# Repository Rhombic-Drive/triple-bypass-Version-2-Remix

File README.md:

# Triple Bypass Version 2
This is a redesign of the fantastic 3bp from dbElectronics.  The goal of this project was to take the initial design and accommodate all models on one pcb without the need to swap parts. It was a team effort between myself, Retrorgb, and Jose Cruz who did the majorty of the testing. Ace, FirebrandX and Mobiusstriptech all were part of the group that helped with the redesign and added various ideas and suggestions that lead to the final product.  The audio adjustment work was done with the help of the mdFourier tool by Artemio Urbina found here - 
https://github.com/ArtemioUrbina/MDFourier.  Artemio and Bfbii stayed up many late nights and helped me run mdFourier to get the levels to match as close as we could to a model 1 va3 genesis.

From zaxour:
Modified version of Tian Feng/dB_Electronics triple bypass v2 board

Incorporates 5.6k pull up resistors for the RGB lines, as Model 1 3BP installs lift the VDP pins to isolate them from the Genesis/MD PCB. Based on research by Tian Feng, and subsequently verified by myself by looking at all available schematics for the Model 1 Genesis/MD, this causes a loss of fidelity in color transitions.

# Installation Instructions

Currently I suggest using the Audio installation instructions from the mega amp 2.0
http://www.sega-16.com/forum/showthread.php?31989-Take-your-Genesis-audio-to-the-next-level-The-Mega-Amp-2-0-is-here!

For rgb bypass instructions, please see https://www.retrorgb.com/genesistriplebypass.html for now. I will continue working on getting more up-to-date instructions.

# Confirmed Working
The current version of this is working with no issues and has been tested and measured with mdFourier. There are still some systems where the pull down jumpers have not been confirmed.  If you notice any issues, please let me know.
# Design Files
I designed this using the online software tool Easyeda. While I have made the file open for people to edit, I have not yet been able to allow for the files to be truly open source.  This is a work in progress and if I have to remake everything from scratch in Kicad. The files here will always be the most up to date versions. 
# Change Log 17/03/2020
I have added a kicad file to the folder.  it looks ok but I still see some issues with ground layers.  I am new to kicad but this pretty damn close.  As it stands, I still recommend using the current gerber files to send to a pcd fab.  The design files are good to go if you want to to change or modify the design.  
# Change Log 06/03/2020
- Changed the jumper settings on the silk screen to match new info from Jose Cruz that the model 2 va4 has all of the 75 ohm pulldowns on the Genesis. Nothing needs to be changed on the previous versions.  Just take note when installing in a model 2 va4.
# Change Log from V1
 - Added jumpers so that all pulldowns could be enabled or disabled without switching parts.
 - Added AC coupling capacitors on the input of the ths7374 to accommodate for systems that we have not measured or installed in yet.
 - Changed the op amp to a soic8 footprint to accommodate a larger variety of possible op amps.
 - Changed the op amp to a tl972 low noise op amp.
 - Lowered the overall volume and increased resistance to try and alleviate some of the clipping in the louder games.
 - Changed the resistor values and numbering to try and fit on the smaller board.
 - Changed audio and video capacitors to tantalum to accommodate for a bottom mount. 
 - Adjusted and tested installation in a model 1 Genesis. 
 - Increased the audio output capacitors to 47uf.
 - Shrunk the overall size and move the din to the middle of the board to try to avoid the power jacks on a bottom install. 
 - Changed the Low pass filter to a solder jumper that will enable when it is jumped.

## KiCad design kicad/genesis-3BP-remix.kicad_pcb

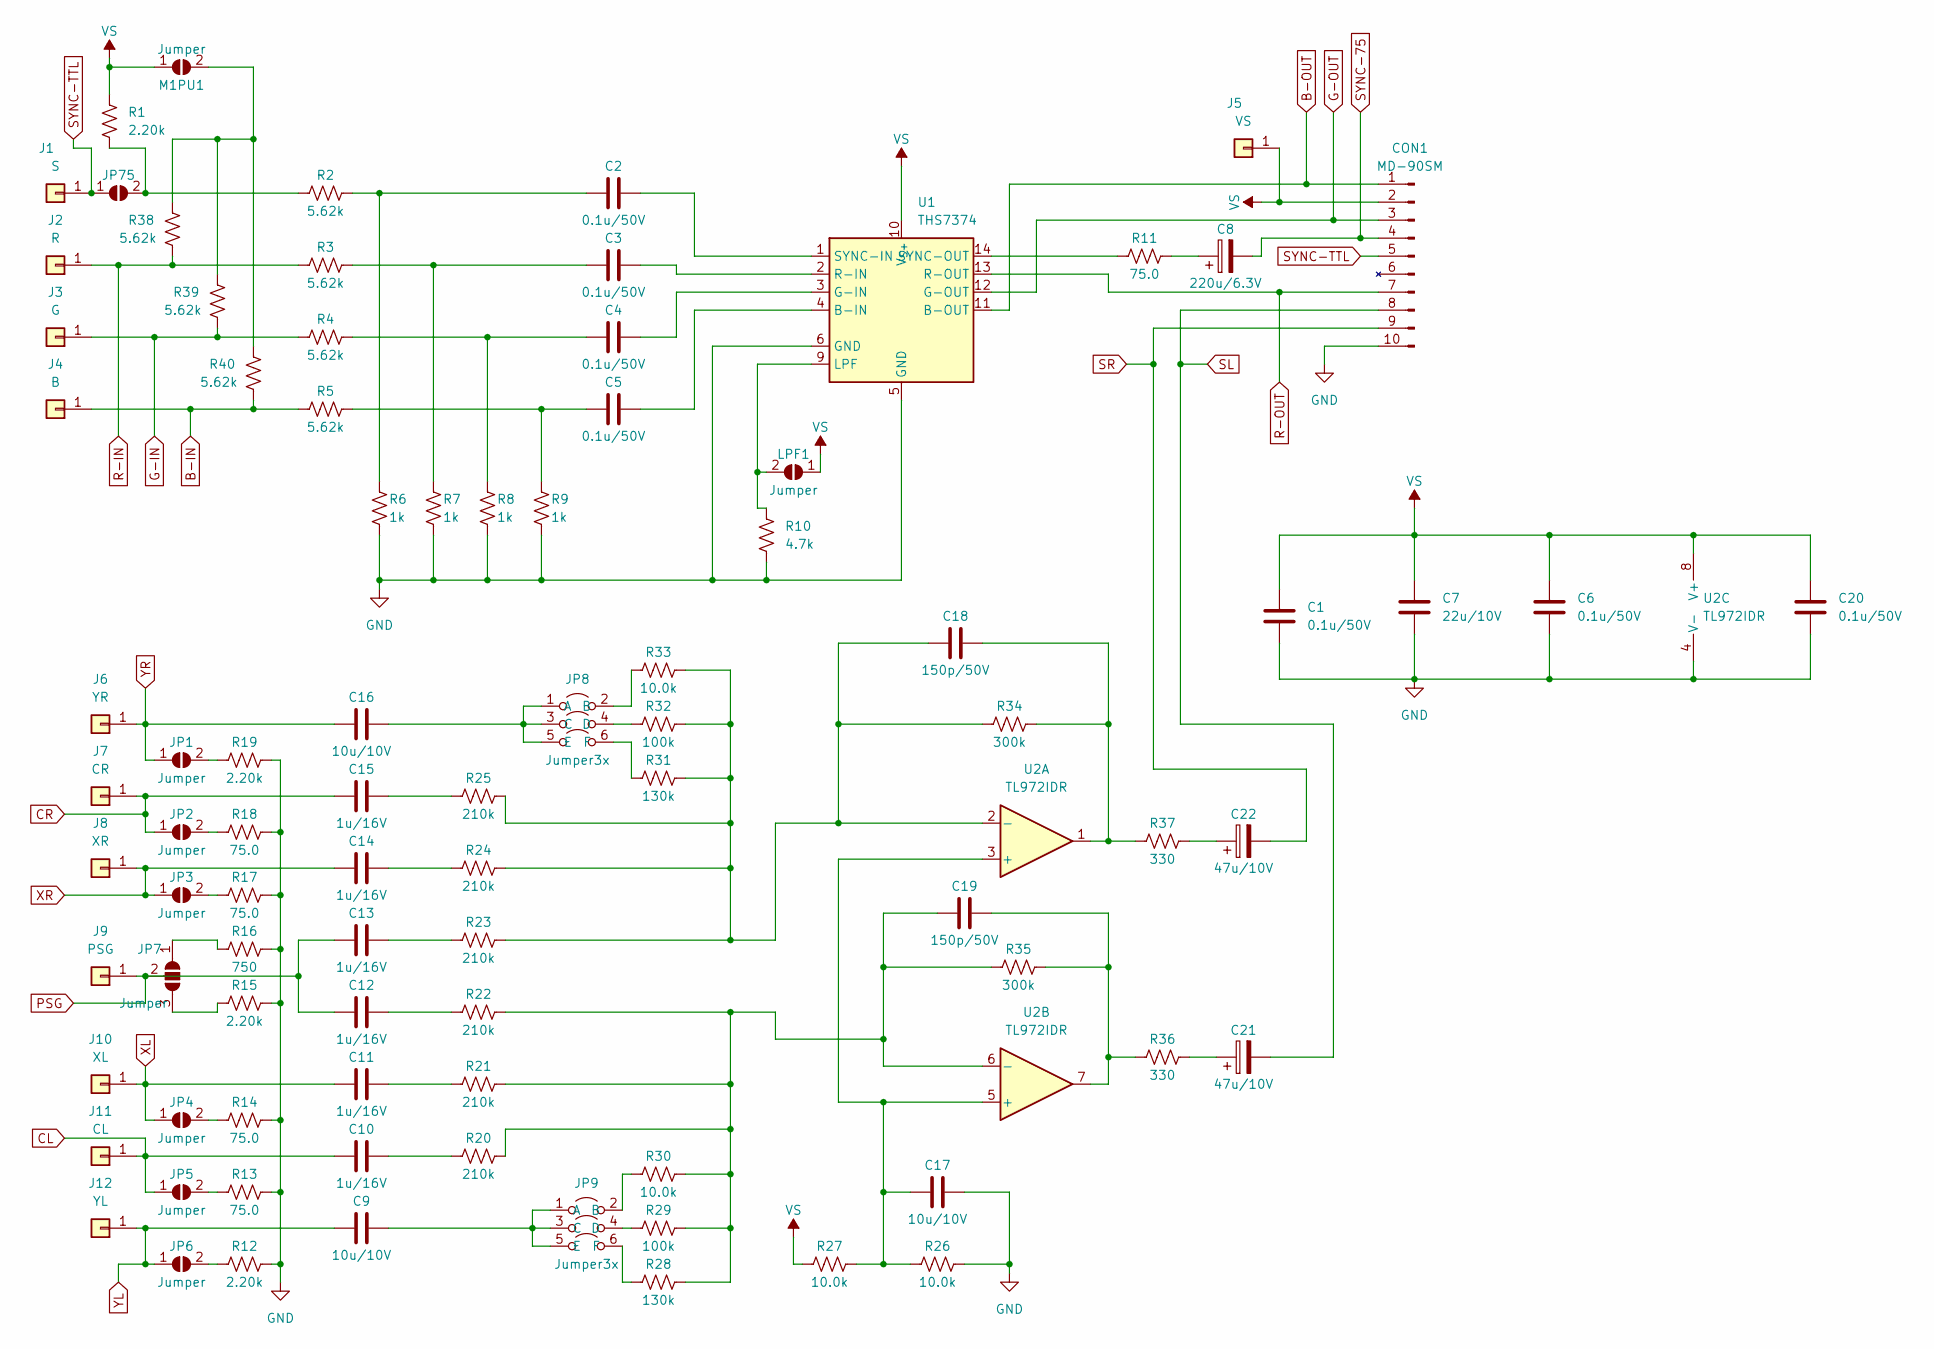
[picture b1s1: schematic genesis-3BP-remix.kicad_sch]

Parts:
C1, C2, C3, C4, C5, C6, C20: 0.1u/50V; C_0603_1608Metric
C7: 22u/10V; C_1210_3225Metric
C8: 220u/6.3V; CP_EIA-3528-15_AVX-H
C9, C16: 10u/10V; C_0805_2012Metric
C10, C11, C12, C13, C14, C15: 1u/16V; C_0603_1608Metric
C17: 10u/10V; CP_EIA-3216-18_Kemet-A
C18, C19: 150p/50V; C_0603_1608Metric
C21, C22: 47u/10V; CP_EIA-3528-15_AVX-H
CON1: MD-90SM
J1: S; Solder Pad
J2: R; Solder Pad
J3: G; Solder Pad
J4: B; Solder Pad
J5: VS; Solder Pad
J6: YR; Solder Pad
J7: CR; Solder Pad
J8: XR; Solder Pad
J9: PSG; Solder Pad
J10: XL; Solder Pad
J11: CL; Solder Pad
J12: YL; Solder Pad
JP1, JP2, JP3, JP4, JP5, JP6, JP75: Jumper; Jumper Pad 2
JP7: Jumper; Jumper Pad 3
JP8, JP9: Jumper3x; Triple Jumper
LPF1: Jumper; Jumper Pad 2
M1PU1: Jumper; Jumper Pad 2
R1, R12, R15, R19: 2.20k; R_0603_1608Metric
R2, R3, R4, R5, R38, R39, R40: 5.62k; R_0603_1608Metric
R6, R7, R8, R9: 1k; R_0603_1608Metric
R10: 4.7k; R_0603_1608Metric
R11, R13, R14, R17, R18: 75.0; R_0603_1608Metric
R16: 750; R_0603_1608Metric
R20, R21, R22, R23, R24, R25: 210k; R_0603_1608Metric
R26, R27, R30, R33: 10.0k; R_0603_1608Metric
R28, R31: 130k; R_0603_1608Metric
R29, R32: 100k; R_0603_1608Metric
R34, R35: 300k; R_0603_1608Metric
R36, R37: 330; R_0603_1608Metric
U1: THS7374; TSSOP-14_4.4x5mm_P0.65mm
U2: TL972IDR; SOIC-8_3.9x4.9mm_P1.27mm

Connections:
B-IN: J4.1, R5.1, R40.1
B-OUT: CON1.1, U1.11 (B-OUT)
CL: C10.1, J11.1, JP5.1 (A)
CR: C15.1, J7.1, JP2.1 (A)
G-IN: J3.1, R4.1, R39.1
G-OUT: CON1.3, U1.12 (G-OUT)
GND: C1.2, C6.1, C7.1, C17.2, C20.1, CON1.10, R6.1, R7.1, R8.1, R9.1, R10.1, R12.2, R13.2, R14.2, R15.2, R16.2, R17.2, R18.2, R19.2, R26.2, U1.5 (GND), U1.6 (GND), U2.4 (V-)
unnamed: C2.1, R2.2, R6.2
unnamed: C3.1, R3.2, R7.2
unnamed: C4.1, R4.2, R8.2
unnamed: C5.1, R5.2, R9.2
unnamed: C8.1, R11.1
unnamed: C10.2, R20.1
unnamed: C11.2, R21.1
unnamed: C12.2, R22.1
unnamed: C13.2, R23.1
unnamed: C14.2, R24.1
unnamed: C15.2, R25.1
unnamed: C18.2, R34.2, R37.1, U2.1
unnamed: C19.2, R35.2, R36.1, U2.7
unnamed: C21.1, R36.2
unnamed: C22.1, R37.2
unnamed: JP1.2 (B), R19.1
unnamed: JP2.2 (B), R18.1
unnamed: JP3.2 (B), R17.1
unnamed: JP4.2 (B), R14.1
unnamed: JP5.2 (B), R13.1
unnamed: JP6.2 (B), R12.1
unnamed: JP7.1 (A), R16.1
unnamed: JP7.3 (B), R15.1
unnamed: C16.2, JP8.1 (A), JP8.3 (C), JP8.5 (E)
unnamed: JP8.2 (B), R33.1
unnamed: JP8.4 (D), R32.1
unnamed: JP8.6 (F), R31.1
unnamed: C9.2, JP9.1 (A), JP9.3 (C), JP9.5 (E)
unnamed: JP9.2 (B), R30.1
unnamed: JP9.4 (D), R29.1
unnamed: JP9.6 (F), R28.1
unnamed: JP75.2 (B), R1.1, R2.1
unnamed: LPF1.2 (B), R10.2, U1.9 (LPF)
unnamed: M1PU1.2 (B), R38.2, R39.2, R40.2
unnamed: C5.2, U1.4 (B-IN)
unnamed: C4.2, U1.3 (G-IN)
unnamed: C3.2, U1.2 (R-IN)
unnamed: C2.2, U1.1 (SYNC-IN)
unnamed: R11.2, U1.14 (SYNC-OUT)
unnamed: C17.1, R26.1, R27.2, U2.3 (+), U2.5 (+)
unnamed: C18.1, R23.2, R24.2, R25.2, R31.2, R32.2, R33.2, R34.1, U2.2 (-)
unnamed: C19.1, R20.2, R21.2, R22.2, R28.2, R29.2, R30.2, R35.1, U2.6 (-)
PSG: C12.1, C13.1, J9.1, JP7.2 (C)
R-IN: J2.1, R3.1, R38.1
R-OUT: CON1.7, U1.13 (R-OUT)
SL: C21.2, CON1.8
SR: C22.2, CON1.9
SYNC-75: C8.2, CON1.4
SYNC-TTL: CON1.5, J1.1, JP75.1 (A)
VS: C1.1, C6.2, C7.2, C20.2, CON1.2, J5.1, LPF1.1 (A), M1PU1.1 (A), R1.2, R27.1, U1.10 (V_{S+}), U2.8 (V+)
XL: C11.1, J10.1, JP4.1 (A)
XR: C14.1, J8.1, JP3.1 (A)
YL: C9.1, J12.1, JP6.1 (A)
YR: C16.1, J6.1, JP1.1 (A)

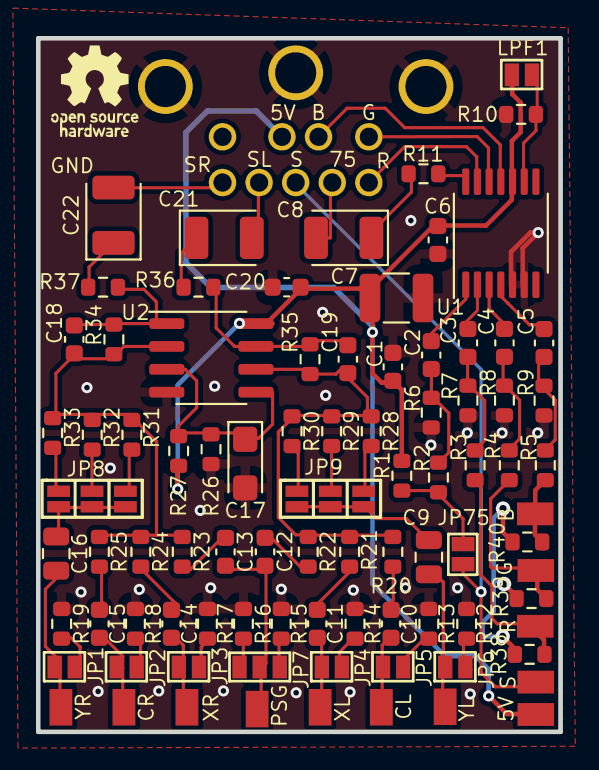
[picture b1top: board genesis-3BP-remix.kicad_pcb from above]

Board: 2 copper layers, 29.0 x 38.5 mm, 91 parts (1 on the bottom side), 61 nets.

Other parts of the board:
G: LOGO; OSHW-LOGO_5MM
G#2: LOGO; OSHW-LOGO_5MM

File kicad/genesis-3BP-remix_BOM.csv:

Designator,Footprint,Quantity,Designation,Supplier and ref
"C1,C2,C3,C4,C5,C6,C20",C_0603_1608Metric,7,0.1u/50V,C0603C104M5RACTU
"C10,C11,C12,C13,C14,C15",C_0603_1608Metric,6,1u/16V,C0603C105K4PACTU
C17,CP_EIA-3216-18_Kemet-A,1,10u/10V,TAJA106K016RNJV
"C18,C19",C_0603_1608Metric,2,150p/50V,CL10C151JB8NFNC
"C21,C22",CP_EIA-3528-15_AVX-H,2,47u/10V,TAJB476M010TNJ
C7,C_1210_3225Metric,1,22u/10V,C3225X7R1A226K230AC
C8,CP_EIA-3528-15_AVX-H,1,220u/6.3V,TCOB0J227M8R-EN1
"C9,C16",C_0805_2012Metric,2,10u/10V,EMK212BJ106KG-T
"R1,R12,R15,R19",R_0603_1608Metric,4,2.20k,RK73H1JTTD2201F
R10,R_0603_1608Metric,1,4.7k,RK73H1JTTD4701F
"R11,R13,R14,R17,R18",R_0603_1608Metric,5,75R,RK73H1JTTDD75R0F
R16,R_0603_1608Metric,1,750R,CR0603-FX-7500ELF
"R2,R3,R4,R5,R38,R39,R40",R_0603_1608Metric,7,5.62k,RK73H1JTTD5621F
"R20,R21,R22,R23,R24,R25",R_0603_1608Metric,6,210k,RK73H1JTTD2103F
"R26,R27,R30,R33",R_0603_1608Metric,4,10.0k,RK73H1JTTD1002F
"R28,R31",R_0603_1608Metric,2,130k,CR0603-FX-1303ELF
"R29,R32",R_0603_1608Metric,2,100k,RK73H1JTTD1003F
"R34,R35",R_0603_1608Metric,2,300k,RK73H1JTTD3003F
"R36,R37",R_0603_1608Metric,2,330R,RK73H1JTTD3300F
"R6,R7,R8,R9",R_0603_1608Metric,4,1k,RK73H1JTTD1001F
U1,TSSOP-14_4.4x5mm_P0.65mm,1,THS7374IPWR,THS7374IPWR
U2,SOIC-8_3.9x4.9mm_P1.27mm,1,TL972IDR,TL972IDR

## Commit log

2024-01-12 Updated schematic
2024-01-12 Adding new KiCad files
2024-01-12 Delete kicad/Schematic_3bp v2-remix_2024-01-12.png
    Duplicate
2024-01-12 New BOM
2024-01-12 Update cap pad change
2024-01-12 Update gerbers
2024-01-16 Update BOM
2024-01-16 Update silkscreen placement
2024-01-16 New schematic

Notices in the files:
kicad/genesis-3BP-remix.kicad_pcb:
Licensed under CERN OHL v.1.2
